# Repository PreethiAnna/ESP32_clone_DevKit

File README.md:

ESP32 clone project is a 4-layer ESP32 development module.
It is a clone of ESP32 devkitc v4.

Credits- Mr.Peter Dalmaris and the book "Kicad like a pro: Advanced projects and recipes"

Schematic of the project

Layout 

3D visualization (Front & back)

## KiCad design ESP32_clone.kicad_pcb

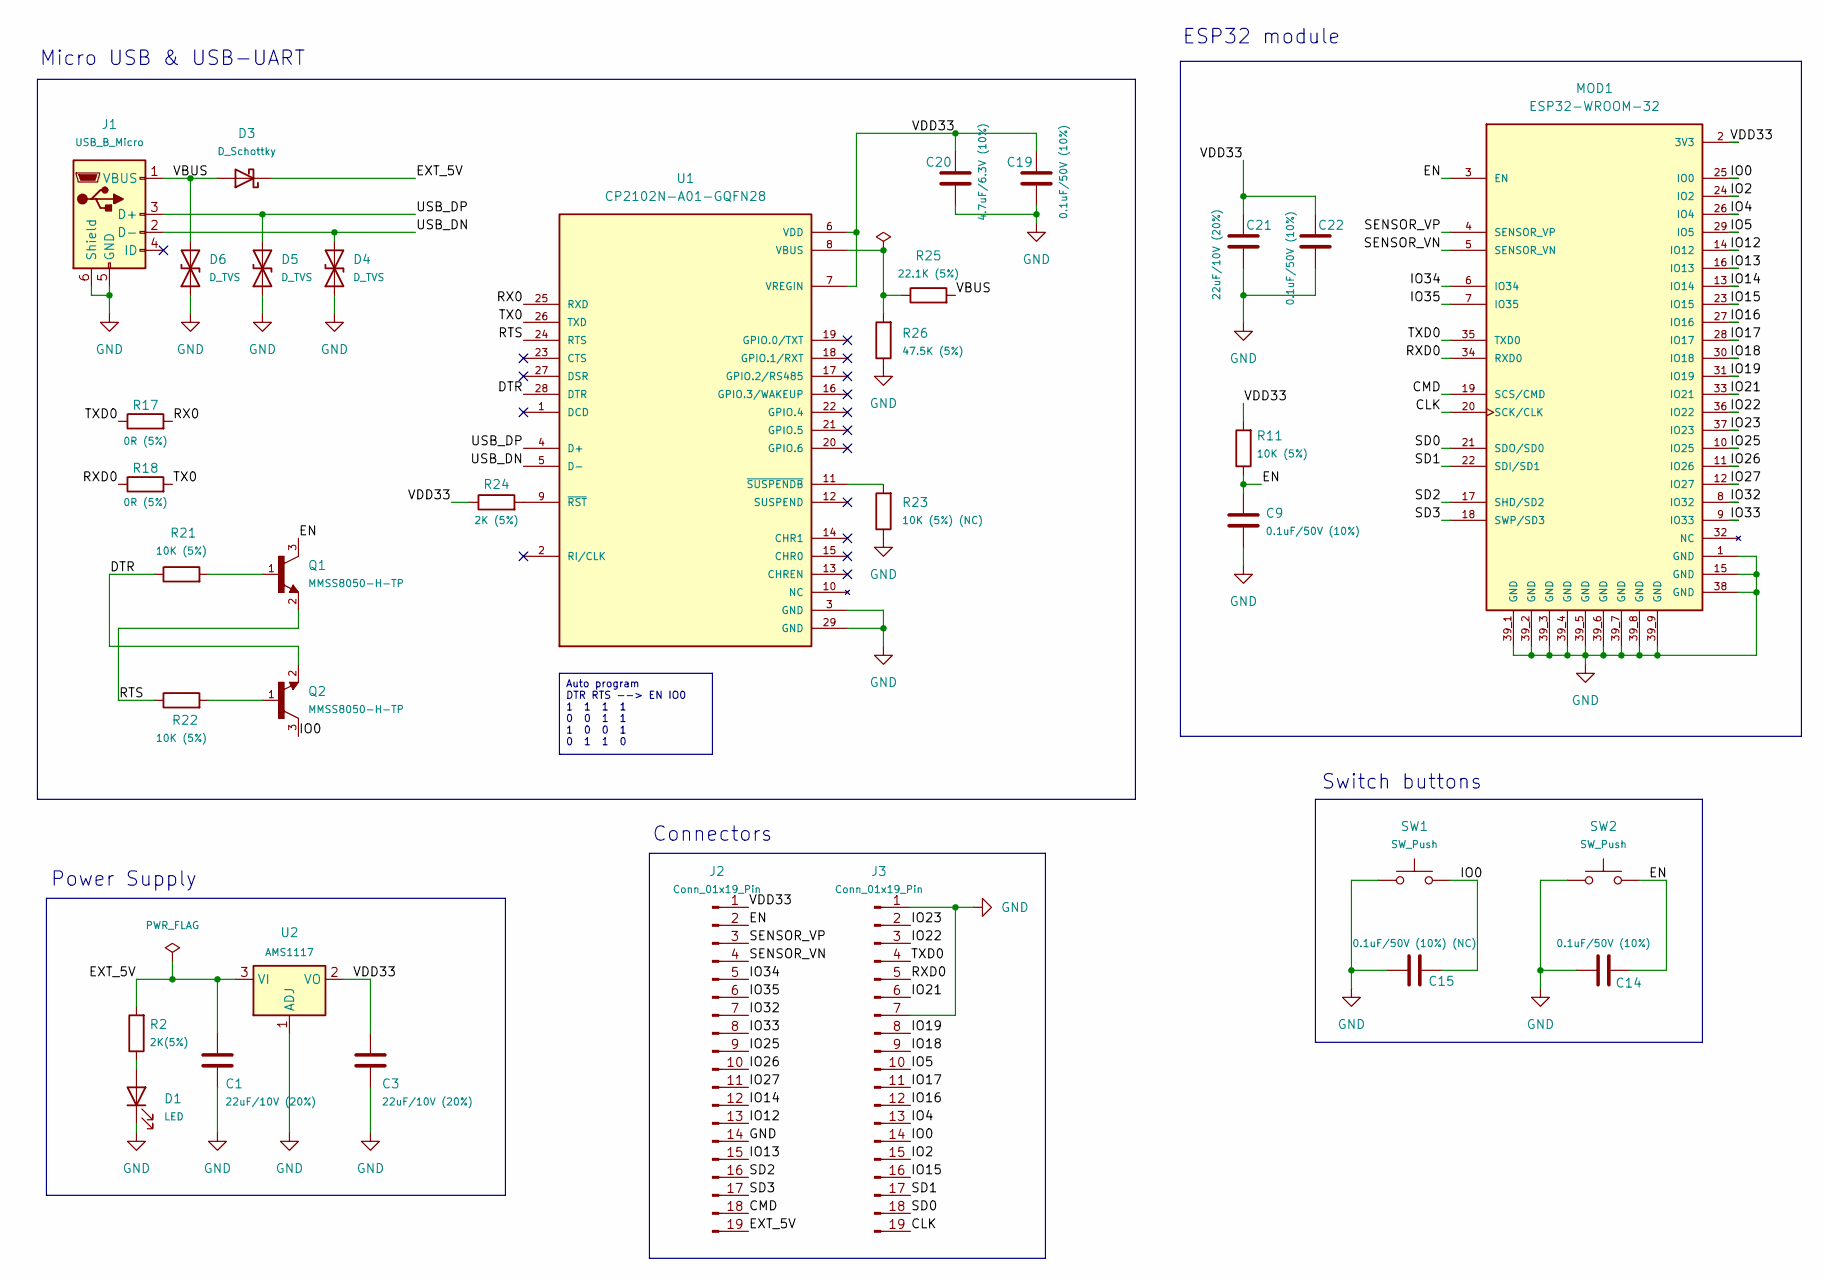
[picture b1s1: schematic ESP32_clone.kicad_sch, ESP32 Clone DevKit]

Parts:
C1, C3, C21: 22uF/10V (20%); C_0201_0603Metric
C9, C14, C19, C22: 0.1uF/50V (10%); C_01005_0402Metric
C15: 0.1uF/50V (10%) (NC); C_01005_0402Metric
C20: 4.7uF/6.3V (10%); C_01005_0402Metric
D1: LED; LED_0603_1608Metric
D3: D_Schottky; D_SOD-323
D4, D5, D6: D_TVS; D_SOD-523
J1: USB_B_Micro; USB_Micro-AB_Molex_47590-0001
J2, J3: Conn_01x19_Pin; PinHeader_1x19_P2.54mm_Vertical
MOD1: ESP32-WROOM-32; MODULE_ESP32-WROOM-32; MPN ESP32-WROOM-32
Q1, Q2: MMSS8050-H-TP; SOT-23-3; MPN MMSS8050-H-TP
R2: 2K(5%); R_01005_0402Metric
R11, R21, R22: 10K (5%); R_01005_0402Metric
R17, R18: 0R (5%); R_01005_0402Metric
R23: 10K (5%) (NC); R_01005_0402Metric
R24: 2K (5%); R_01005_0402Metric
R25: 22.1K (5%); R_01005_0402Metric
R26: 47.5K (5%); R_01005_0402Metric
SW1, SW2: SW_Push; SW_SPST_B3S-1000
U1: CP2102N-A01-GQFN28; TQFN-28-1EP_5x5mm_P0.5mm_EP2.7x2.7mm; MPN CP2102N-A01-GQFN28
U2: AMS1117; SOT-223-3_TabPin2

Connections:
/CLK: J3.19, MOD1.20 (SCK/CLK)
/CMD: J2.18, MOD1.19 (SCS/CMD)
/DTR: Q2.2, R21.1, U1.28 (DTR)
/EN: C9.1, C14.2, J2.2, MOD1.3 (EN), Q1.3, R11.1, SW2.2
/EXT_5V: C1.1, D3.1 (K), J2.19, R2.2, U2.3 (VI)
/IO0: C15.2, J3.14, MOD1.25 (IO0), Q2.3, SW1.2
/IO2: J3.15, MOD1.24 (IO2)
/IO4: J3.13, MOD1.26 (IO4)
/IO5: J3.10, MOD1.29 (IO5)
/IO12: J2.13, MOD1.14 (IO12)
/IO13: J2.15, MOD1.16 (IO13)
/IO14: J2.12, MOD1.13 (IO14)
/IO15: J3.16, MOD1.23 (IO15)
/IO16: J3.12, MOD1.27 (IO16)
/IO17: J3.11, MOD1.28 (IO17)
/IO18: J3.9, MOD1.30 (IO18)
/IO19: J3.8, MOD1.31 (IO19)
/IO21: J3.6, MOD1.33 (IO21)
/IO22: J3.3, MOD1.36 (IO22)
/IO23: J3.2, MOD1.37 (IO23)
/IO25: J2.9, MOD1.10 (IO25)
/IO26: J2.10, MOD1.11 (IO26)
/IO27: J2.11, MOD1.12 (IO27)
/IO32: J2.7, MOD1.8 (IO32)
/IO33: J2.8, MOD1.9 (IO33)
/IO34: J2.5, MOD1.6 (IO34)
/IO35: J2.6, MOD1.7 (IO35)
/RTS: Q1.2, R22.1, U1.24 (RTS)
/RX0: R17.2, U1.25 (RXD)
/RXD0: J3.5, MOD1.34 (RXD0), R18.1
/SD0: J3.18, MOD1.21 (SDO/SD0)
/SD1: J3.17, MOD1.22 (SDI/SD1)
/SD2: J2.16, MOD1.17 (SHD/SD2)
/SD3: J2.17, MOD1.18 (SWP/SD3)
/SENSOR_VN: J2.4, MOD1.5 (SENSOR_VN)
/SENSOR_VP: J2.3, MOD1.4 (SENSOR_VP)
/TX0: R18.2, U1.26 (TXD)
/TXD0: J3.4, MOD1.35 (TXD0), R17.1
/USB_DN: D4.2 (A2), J1.2 (D-), U1.5 (D-)
/USB_DP: D5.2 (A2), J1.3 (D+), U1.4 (D+)
/VBUS: D3.2 (A), D6.2 (A2), J1.1 (VBUS), R25.2
/VDD33: C3.1, C19.1, C20.1, C21.1, C22.1, J2.1, MOD1.2 (3V3), R11.2, R24.1, U1.6 (VDD), U1.7 (VREGIN), U2.2 (VO)
GND: C1.2, C3.2, C9.2, C14.1, C15.1, C19.2, C20.2, C21.2, C22.2, D1.1 (K), D4.1 (A1), D5.1 (A1), D6.1 (A1), J1.5 (GND), J1.6 (Shield), J2.14, J3.1, J3.7, MOD1.1 (GND), MOD1.15 (GND), MOD1.38 (GND), MOD1.39_1 (GND), MOD1.39_2 (GND), MOD1.39_3 (GND), MOD1.39_4 (GND), MOD1.39_5 (GND), MOD1.39_6 (GND), MOD1.39_7 (GND), MOD1.39_8 (GND), MOD1.39_9 (GND), R23.1, R26.1, SW1.1, SW2.1, U1.3 (GND), U1.29 (GND), U2.1 (ADJ)
unnamed: D1.2 (A), R2.1
unnamed: Q1.1, R21.2
unnamed: Q2.1, R22.2
unnamed: R25.1, R26.2, U1.8 (VBUS)
unnamed: R24.2, U1.9 (~RST)
unnamed: R23.2, U1.11 (~SUSPENDB)

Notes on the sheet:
Auto program DTR RTS --> EN IO0 1 1 1 1 0 0 1 1 1 0 0 1 0 1 1 0
ESP32 module
Switch buttons
Micro USB & USB-UART
Connectors
Power Supply

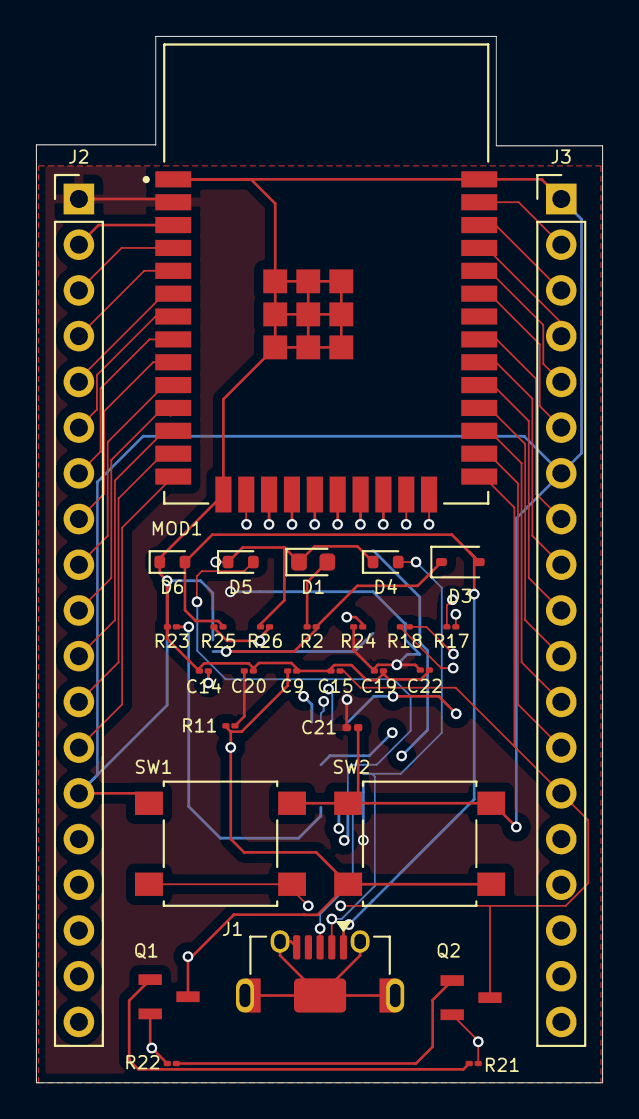
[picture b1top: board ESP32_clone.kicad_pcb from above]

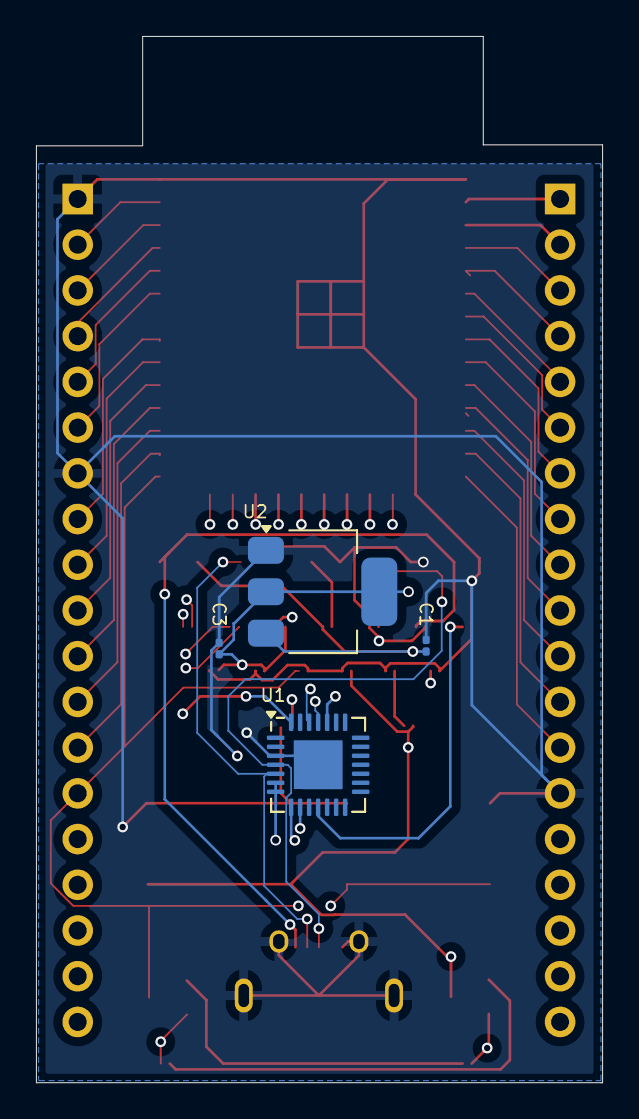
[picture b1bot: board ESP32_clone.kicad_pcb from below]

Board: 4 copper layers, 31.5 x 58.1 mm, 34 parts (4 on the bottom side), 49 nets.
